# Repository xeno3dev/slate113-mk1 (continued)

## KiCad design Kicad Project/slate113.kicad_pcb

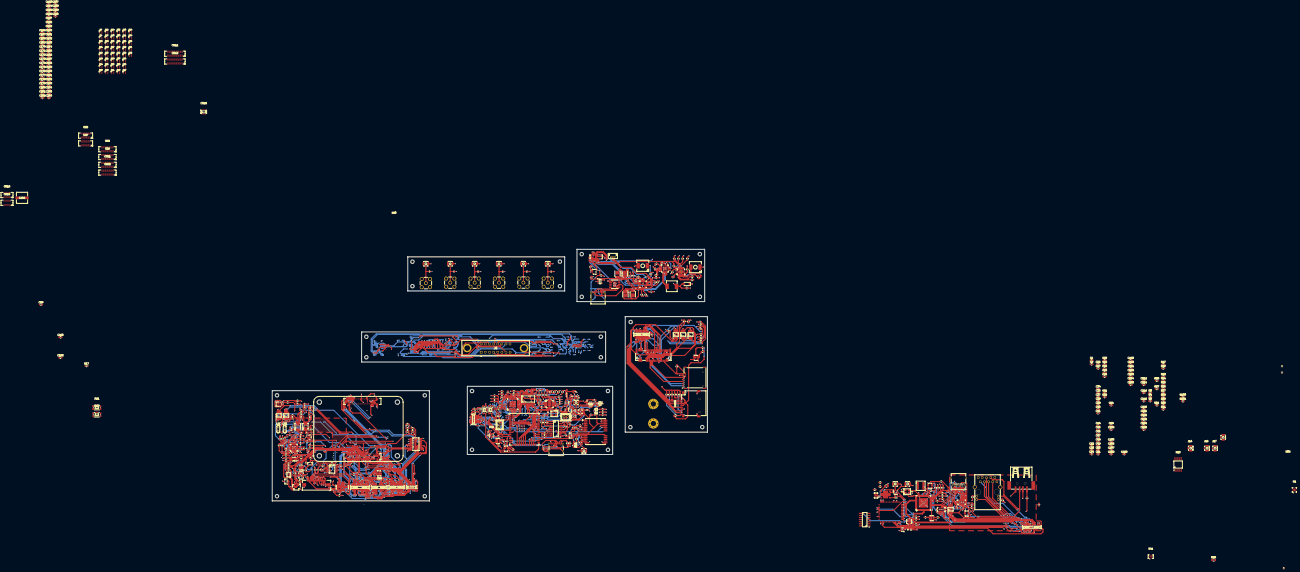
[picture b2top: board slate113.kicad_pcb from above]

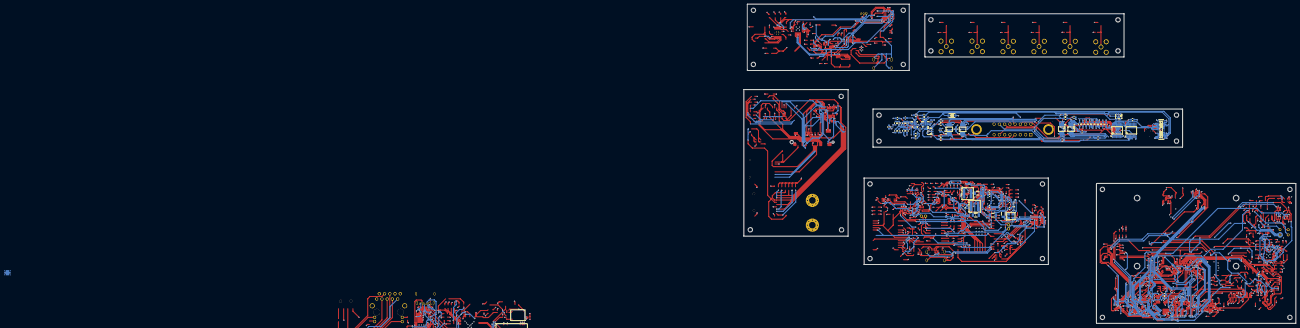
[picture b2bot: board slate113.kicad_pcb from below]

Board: 8 copper layers, 267.6 x 154.7 mm, 611 parts (73 on the bottom side), 545 nets.

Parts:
C1, C94, C106, C108: 0.1µF; C_0603_1608Metric
C2, C8, C9: 1.0µF; C_0603_1608Metric
C3, C11, C68, C71, C91, C217: 4.7µF; C_0603_1608Metric
C4, C5: 47nF; C_0603_1608Metric
C6, C7, C10, C20, C61, C89, C116, C131, C135, C137, C140, C145, C165, C216: 10µF; C_0603_1608Metric
C12, C19, C32, C42, C72, C74, C75, C79, C95, C97, C117, C123, C141, C228: 2.2µF; C_0603_1608Metric
C13, C21, C22, C23, C24, C25, C26, C27, C30, C31, C33, C34, C36, C37, C38, C39, C40, C41, C43, C44, C45, C46, C47, C48, C49, C50, C51, C52, C53, C54, C55, C56, C57, C58, C59, C62, C67, C69, C70, C73, C77, C78, C84, C90, C92, C96, C98, C111, C114, C115, C133, C134, C136, C139, C142, C147, C148, C149, C151, C152, C153, C154, C158, C159, C160, C161, C162, C163, C164, C166, C167, C168, C169, C170, C171, C172, C173, C174, C175, C176, C177, C178, C179, C180, C181, C182, C183, C184, C185, C186, C187, C188, C189, C190, C191, C192, C193, C194, C195, C196, C197, C198, C199, C200, C201, C202, C203, C204, C205, C206, C207, C208, C209, C210, C211, C212, C214, C215, C218, C219, C220, C221, C222, C223, C224, C225, C229, C236: 100nF; C_0603_1608Metric
C14: 8.2nF; C_0603_1608Metric
C15, C18, C76, C118, C120, C121, C124, C129, C130, C132, C138, C144, C150, C155, C239: 1µF; C_0603_1608Metric
C16, C125, C126, C127, C128, C244, C245: 1nF; C_0603_1608Metric
C17: 68pF; C_0603_1608Metric
C28, C29, C35, C66: 15pF; C_0402_1005Metric
C60: 1.8pF; C_0402_1005Metric
C63, C83, C86, C99, C100, C104, C105, C107, C119, C122, C156: 100pF; C_0603_1608Metric
C64: 6.8pF; C_0402_1005Metric
C65, C231: 6.8 pF ± 0.5 pF; C_0402_1005Metric
C80, C240, C242: 10nF; C_0603_1608Metric
C81: 6.8nF; C_0603_1608Metric
C82, C233, C234, C243, C246: 100nF; C_0402_1005Metric
C85, C232: 220 pF ± 5%; C_0402_1005Metric
C87, C88: 33pF; C_0603_1608Metric
C93, C102: 8.2pF; C_0402_1005Metric
C101: 100pF; C_0402_1005Metric
C103: 8.2pF; C_0603_1608Metric
C109, C112: 22pF; C_0402_1005Metric
C110, C113: 22pF; C_0603_1608Metric
C143, C146: 3.3nF; C_0603_1608Metric
C157: 4.7µF/10V/Ceramic; C_0603_1608Metric
C213: 47µF; C_0805_2012Metric
C226, C227: 18pF; C_0402_1005Metric
C230: 12 pF ± 5%; C_0402_1005Metric
C235: 220 µF; CHEMI-F61
C237, C238, C241: 220pF; C_0402_1005Metric
CN1, CN2: DF40C-50DP-0.4V; CONN-SMD_DF40C-50DP-0.4V
CN3, CN7: DF40C-30DS-0.4V; CONN-SMD_DF40C-30DS-0.4V51
CN4, CN6, CN21, CN22: DF40C-40DS-0.4V; CONN-SMD_DF40C-40DS-0.4V51
CN5, CN8, CN9, CN10: DF40C-40DP-0.4V; CONN-SMD_DF40C-40DP-0.4V
CN11, CN14: DF40C-30DP-0.4V; CONN-SMD_30P-P0.40_5001-BM0430-15-00
CN12, CN13: DF40C-50DS-0.4V; CONN-SMD_DF40C-50DS-0.4V51
CN15, CN16: DF40C-24DS-0.4V; CONN-SMD_DF40C-24DS-0.4V51
CN17: 530480310; CONN-TH_0530470310
CN18: DF40C-10DP-0.4V; CONN-SMD_10P-P0.40_DF40C-10DP-0.4V-51
CN19, CN20: DF40C-24DP-0.4V; CONN-SMD_DF40C-24DP-0.4V
Card1: NANO SIM 7P 1.37H PUSH; SIM-SMD_YKSIM-PUSH137-140NANO
Card2: TF PUSH; TF-SMD_TF-PUSH
D1: B5819W; D_SOD-123
D2: RCLAMP0521PATCT; D0402-BI
D3, D4: PESD3V3U1UL; SOD-882_L1.0-W0.6-RD
D5, D6: SP0504BAHTG; SOT-23-5_L3.0-W1.7-P0.95-LS2.8-BR
D7: SMF5.0A_C151296; SOD-123F_L2.8-W1.8-LS3.7-RD
D8, D9, D10, D11, D12, D13, D14, D15, D16, D17, D18, D19, D20, D21, D22, D23, D24, D25, D26, D27, D28, D29, D30, D31, D32, D33, D34, D35, D36, D37, D38, D39, D40, D41, D42, D43, D44, D45, D46, D47, D48, D49, D50, D51, D52: SK9822-EC20
F1: Polyfuse; Fuse_0603_1608Metric
FB1, FB2, FB3, FB5, FB11: FerriteBead; L_0603_1608Metric
FB6, FB7, FB8, FB9: 600Ω @ 100MHz; L_0603_1608Metric
FB10: FerriteBead_Small; L_0603_1608Metric
FPC1: FPC0.5-24P; FPC-SMD_P0.50-24P_XJ-FGS
FPC2: FPC-0.5FX-6PWBH10; FPC-SMD_FPC-0.5FX-6PWBH10
H5, H6: MountingHole_Pad; MountingHole_3.2mm_M3_Pad_Via
J1, J8, J11, J22, J23, J25: RFPC-SMA27-F; GRADCONN_RFPC-SMA27-F
J2: TYPE-C16PIN; USB-C-SMD_TYPE-C16PIN
J3, J7, J10, J12, J24, J26: Conn_Coaxial; U.FL_Hirose_U.FL-R-SMT-1(10)
J4: DF40C-100DP-0.4V51*2; Raspberry-Pi-4-Compute-Module
J6: 395-016-520-202; 395016520202
J9: Bus_M.2_Socket_B; NGFFM_2BKEY_8_2_COPY
J13, J14, J15, J16, J17, J18, J19, J20: U.FL; IPEX-SMD_BWIPX-1-001E
L1: 4.7µH; IND-SMD_L5.5-W5.3
L2, L4: 1µH; IND-SMD_L7.1-W6.5-P5.60
L3: 10µH; IND-SMD_L7.1-W6.6
L5: 5.6nH; L_0402_1005Metric
L6, L7, L9, L10: 33 nH ± 5%; L_0402_1005Metric
L8: 68nH; L_0402_1005Metric
L11, L12: YSPIT0520A-R16M; IND-SMD_L5.5-W5.3
LS1, LS2: Solder Pad; TestPoint_2Pads_Pitch2.54mm_Drill0.8mm
Q1: MMBT3904-TP; SOT-23-3_L2.9-W1.3-P1.90-LS2.4-BR
Q4: MMBT3904-C20526; SOT-23-3_L2.9-W1.3-P1.90-LS2.4-BR
Q5, Q6, Q7, Q8: CSD17575Q3; VSON-CLIP-8_L3.3-W3.3-P0.65-BL
R1: 3.0kΩ (1s, 1.5MHz); R_0603_1608Metric
R2, R25, R31, R32, R33, R36, R37, R47, R50, R52, R53, R54, R55, R64, R74, R75, R76, R84, R88, R90, R94, R96, R100, R102, R108, R109, R110, R112, R113, R114, R115, R116, R117, R118, R119, R120, R122, R124, R126, R127, R128, R129, R130, R131, R134, R135, R136, R137, R138, R139, R140, R141, R153: 10kΩ; R_0603_1608Metric
R3, R4, R27, R42, R62, R63, R97, R98, R132, R133: 4.7kΩ; R_0603_1608Metric
R5, R6, R7, R10, R11, R17, R34, R56, R58, R60, R85, R87, R91, R92, R103, R105: 100kΩ; R_0603_1608Metric
R8: 205kΩ; R_0603_1608Metric
R9: 127kΩ; R_0603_1608Metric
R12: 154kΩ; R_0603_1608Metric
R13: 174kΩ; R_0603_1608Metric
R14: 220kΩ; R_0603_1608Metric
R15: 69.8kΩ; R_0603_1608Metric
R16: 12.1kΩ; R_0603_1608Metric
R18, R19, R20, R21, R22, R23, R26, R38, R44: 47kΩ; R_0603_1608Metric
R24, R142, R143, R144, R145, R146: 50Ω; R_0402_1005Metric
R28: 110Ω; R_0603_1608Metric
R29: 120Ω; R_0603_1608Metric
R30, R65, R66, R68, R69, R77, R78, R79, R80, R81, R82, R83: 22Ω; R_0603_1608Metric
R35: 180kΩ; R_0603_1608Metric
R39: 56kΩ ±1%; R_0603_1608Metric
R40, R41, R104: 5.1kΩ; R_0603_1608Metric
R43, R70: 10Ω; R_0603_1608Metric
R45, R46: 50Ω; R_0805_2012Metric
R48, R49, R51: 52.3Ω; R_0402_1005Metric
R57, R59, R61, R101: 20kΩ; R_0603_1608Metric
R67: 33Ω; R_0603_1608Metric
R71, R72, R73: 1kΩ; R_0603_1608Metric
R86, R93: 402kΩ; R_0603_1608Metric
R89, R95: 3.3kΩ; R_0603_1608Metric
R99: 200kΩ; R_0603_1608Metric
R106, R107: 560Ω; R_0603_1608Metric
R147, R151: 1.5Ω; R_1206_3216Metric
R148, R152: 2.7Ω; R_1206_3216Metric
R149, R150: 2.2kΩ; C_0603_1608Metric
RJ1: HR915350C; RJ45-TH_HR915350C_1
SW1, SW2, SW3, SW4: SW_Push; KEY-SMD_KMR2XXGXXX
U1: FUSB302BMPX; MLP-14_L2.5-W2.5-P0.50-BL-EP
U2: CH224K; SSOP-10-1EP_3.9x4.9mm_P1mm_EP2.1x3.3mm
U3: BQ25792RQMR; QFN-29_L4.0-W4.0-P0.40-TL-BQ25792RQMR
U4: AP2112K-3.3TRG1; SOT-25-5_L2.9-W1.6-P0.95-LS2.8-BL
U5: AP2112K-1.8TRG1; SOT-25_L3.0-W1.6-P0.95-LS2.8-BL
U6: LP8556SQ-E09/NOPB; WQFN-24_L4.0-W4.0-P0.50-BL-EP2.5
U7: HD3SS3220RNHR; WQFN-30_L4.5-W2.5-P0.4-BL-EP
U8: ESD7104MUTAG_C2987068; DFN-10_L2.5-W1.0-P0.50-BL
U9: TPS61088RHLR; VQFN-20_L4.6-W3.6-P0.50-BL
U10, U56, U57, U58: TS3A24159DGSR; MSOP-10_L3.0-W3.0-P0.50-LS5.0-BL
U11, U14, U17, U34, U35, U53, U54: SiP32508DT; TSOT-23-6
U12: PI3USB302-AZBEX; DHVQFN-20_L4.5-W2.5-P0.50-BL-EP
U13: W25Q32JVSSIQ; SOIC-8_L5.3-W5.3-P1.27-LS8.0-BL
U15, U44, U45, U46, U48, U49: TS5A23157DGSR; MSOP-10_L3.0-W3.0-P0.50-LS5.0-BL
U18: GL3523-OTY3C; QFN-76_L9.0-W9.0-P0.40-BL-EP5.8
U19: TXM27.12M0004322DBBDO00T; CRYSTAL-SMD_4P-L3.2-W2.5-BL
U20: CC1101RGPR; QFN-20_L4.0-W4.0-P0.5-TL-EP
U21: 0896BM15A0001001E; SMD6_0896BM15A0001001E_JOT
U22: LC29HBA; LC29H
U23: EM4095HMSO16B+; SOIC-16_L9.9-W3.9-P1.27-LS6.0-BL
U24, U25, U26, U27, U30, U36: PE4259-63; SC-70-6_L2.2-W1.3-P0.65-LS2.1-BL
U28: 0433BM15A0001001E; SMD6_0896BM15A0001001E_JOT
U29: PN7160A1HN/C100E; HVQFN-40_L6.0-W6.0-P0.50-BL-EP4.1
U31, U73: B2B-PH-K-S; CONN-TH_B2B-PH-K-S
U33: ESP32-S3-WROOM-1U-N16R2; WIRELM-SMD_ESP32-S3-WROOM-1U
U37: CPL0605AT13R2455A
U38: X4C60K1-20SR; X4C60K1-20S
U39: XEC24P3-30GR; XEC24P3-30G
U40, U41, U42: AD8317ACPZ-R7; LFCSP-8_L3.0-W2.0-P0.50-BL-EP
U43: LM339D; SOIC-14_L8.7-W3.9-P1.27-LS6.0-BL
U47: ES8388; QFN-28_L4.0-W4.0-P0.45-BL-EP
U50, U51: PAM8302AASCR; MSOP-8_L3.0-W3.0-P0.65-LS5.0-BL
U52: TPS7A0233PDBVR; SOT-23-5_L2.9-W1.6-P0.95-LS2.8-BR
U55, U61: TCA9534APWR; TSSOP-16_L5.0-W4.4-P0.65-LS6.4-BL
U59, U60: TPS259470ARPWR; VQFN-10_L2.0-W2.0-P0.45-TL
U62: PCA9306DCUR; SSOP-8_L2.0-W2.3-P0.50-LS3.1-BR
U63: AP2120N-2.8TRG1; SOT-23-3_L2.9-W1.3-P1.90-LS2.4-BR
U64, U69: TCA9535PWR; TSSOP-24_L7.8-W4.4-P0.65-LS6.4-BL
U65: MSM381ADB001; MIC-SMD_5P_L3.5-W2.7-P0.82_MSM381ADB001
U66: DF40B-10DS-0.4V; CONN-SMD_10P-P0.40_DF40B-10DS-0.4V-51
U67: SIP32508DT-T1-GE3; TSOT-23-6_L2.9-W1.6-P0.95-LS2.8-BR
U68: SN74AHCT125PWR; TSSOP-14_L5.0-W4.4-P0.65-LS6.4-BL
U70: SkyLab WG243; WG243
U71: SKY13373-460LF; QFN-12_L2.0-W2.0-P0.50-BL-EP
U72: SN74AXC1T45DCKR; SC-70-6_L2.0-W1.3-P0.65-LS2.1-BL-1
USB1: TYPE-C 24P QCHT; TYPE-C-SMD_TYPE-C-24P-QCHT
USB2: TYPE-C16PIN; USB-C-SMD_TYPE-C16PIN
USB3: BX-TYPE-A-MWT4P; USB-A-SMD_BX-TYPE-A-MWT4P
X1: X322525MOB4SI; CRYSTAL-SMD_4P-L3.2-W2.5-BL_X322525MOB4SI
Y3: 26.0MHz; CRYSTAL-SMD_4P-L3.2-W2.5-BL

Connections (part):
1V8: C111.1, CN3.5, CN4.38, CN6.38, CN7.5, CN9.38, CN10.38, CN11.5, CN14.5, FPC1.22, J4.88, J4.90, R62.1, R63.2, R71.2, R72.2, R96.1, R97.2, R98.1, R100.2, U5.5 (VOUT), U44.8 (V+), U45.8 (V+), U46.8 (V+), U47.2 (DVDD), U47.3 (PVDD), U48.8 (V+), U49.8 (V+), U62.2 (VREF1)
2.4G_SENSE: CN1.47, CN1.48, CN2.47, CN2.48, CN12.47, CN12.48, CN13.47, CN13.48, J4.47, J4.94, R53.2, R54.2, U43.1, U43.2
3V3: C1.1, C2.1, C8.1, C9.1, C12.1, C19.1, C22.2, C23.2, C24.2, C30.1, C34.1, C41.1, C42.1, C59.2, C82.1, C94.1, C95.1, C99.1, C105.1, C106.1, C107.1, C108.1, C141.1, C148.1, C149.1, C150.1, C151.1, C152.1, C153.1, C154.1, C158.1, C159.1, C160.1, C161.1, C225.1, C233.1, CN1.6, CN1.7, CN2.6, CN2.7, CN3.4, CN4.25, CN5.11, CN6.25, CN7.4, CN8.11, CN9.25, CN10.25, CN11.4, CN12.6, CN12.7, CN13.6, CN13.7, CN14.4, CN15.14, CN16.14, CN19.14, CN20.14, CN21.11, CN22.11, FPC1.23, J4.84, J4.86, J6.3, L4.1, R3.1, R4.1, R7.1, R18.2, R19.2, R20.2, R21.2, R22.2, R23.2, R25.1, R27.1, R28.1, R29.1, R31.1, R32.1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
5V: C97.1, CN15.12, CN16.12, CN20.12
315MHZ_OUT: C232.1, U71.1 (J1)
433MHZ_OUT: U28.1 (UNBALANCEDPORT), U71.9 (J2)
868/915MHZ_OUT: C63.1, U71.3 (J3)
ACC_AUX0: R82.2, U56.3 (COM1)
ACC_AUX1: R83.2, U56.9 (COM2)
ACC_CS0_N: R78.2, U58.9 (COM2)
ACC_IRQ0: R77.2, U57.3 (COM1)
ACC_MISO: R81.2, U58.3 (COM1)
ACC_MOSI: R80.2, U10.9 (COM2)
ACC_RESET_N: R79.2, U57.9 (COM2)
ACC_SCK: R30.2, U10.3 (COM1)
ACDVR1: Q5.4 (G), Q6.4 (G), U3.11 (ACDRV1)
ACDVR2: Q7.4 (G), Q8.4 (G), U3.10 (ACDRV2)
AMP_L_SD: C131.1, C133.1, R74.2, U50.1 (~SD), U69.8 (P04)
AMP_R_SD: C134.1, C135.1, R75.2, U51.1 (~SD), U69.9 (P05)
AUDIO_3V3: C115.1, C116.1, C138.2, R70.2, U47.17 (AVDD), U52.5 (OUT)
AUDIO_ASDOUT: U47.8 (ASDOUT), U49.6 (COM2)
AUDIO_DSDIN: U47.6 (DSDIN), U49.10 (COM1)
AUDIO_I2C_SCL: R62.2, R72.1, U44.4 (NO2), U47.28 (CCLK)
AUDIO_I2C_SDA: R63.1, R71.1, U44.2 (NO1), U47.27 (CDATA)
AUDIO_LOUT1: C130.2, U47.12 (LOUT1)
AUDIO_LRCK: U47.7 (LRCK), U48.6 (COM2)
AUDIO_PCM_CLK: R65.1, U45.2 (NO1)
AUDIO_PCM_CLK_F: C109.1, CN4.21, CN6.21, CN9.21, CN10.21, R65.2, U48.2 (NO1)
AUDIO_PCM_IN: R68.1, U46.2 (NO1)
AUDIO_PCM_IN_F: C112.1, CN4.31, CN6.31, CN9.31, CN10.31, R68.2, U49.4 (NO2)
AUDIO_PCM_OUT: R69.1, U46.4 (NO2)
AUDIO_PCM_OUT_F: C113.1, CN4.30, CN6.30, CN9.30, CN10.30, R69.2, U49.2 (NO1)
AUDIO_PCM_SYNC: R66.1, U45.4 (NO2)
AUDIO_PCM_SYNC_F: C110.1, CN4.32, CN6.32, CN9.32, CN10.32, R66.2, U48.4 (NO2)
AUDIO_ROUT1: C129.1, U47.11 (ROUT1)
AUDIO_SCLK: U47.5 (SCLK), U48.10 (COM1)
AUDIO_VREF: C121.2, U47.10 (VREF)
AVDD9_CAP: C240.2, U20.9 (AVDD)
AVDD11_CAP: C237.2, U20.11 (AVDD)
AVDD14_CAP: C242.2, U20.14 (AVDD)
AVDD15_CAP: C238.2, U20.15 (AVDD)
BADUSB_DM: U33.13 (IO19), USB2.A7 (DN1), USB2.B7 (DN2)
BADUSB_DP: U33.14 (IO20), USB2.A6 (DP1), USB2.B6 (DP2)
BAND_SEL_1: U26.4 (CTRL), U27.4 (CTRL), U64.6 (P02)
BAND_SEL_2: U24.4 (CTRL), U25.4 (CTRL), U64.7 (P03)
BLE_ANT1: U36.5 (RFC), U70.12 (BT)
BLE_CPL: R51.2, U37.4 (Coupled_Out)
BLE_CTRL: CN1.46, CN2.46, CN12.46, CN13.46, J4.49, U36.4 (CTRL)
BLE_DET: U42.4 (VSET), U42.5 (VOUT), U43.8
BLE_REF: R60.2, R61.1, U43.9
BLE_SENSE: CN1.49, CN2.49, CN12.49, CN13.49, J4.96, R55.2, U43.14
BLE_SMA_ANT: J14.1 (In), U37.3 (Output)
BLE_SW_SMA: U36.3 (RF2), U37.2 (Input)
BOOT: SW4.2, U33.27 (IO0)
BQ_INT: CN3.7, CN7.7, CN11.7, CN14.7, J4.19, U3.21 (~INT)
BT_EN: CN1.19, CN2.19, CN12.19, CN13.19, R131.1, U69.4 (P00), U70.38 (BT_DISn)
CC_GDO0: U20.6 (GDO0(ATEST)), U33.6 (IO6)
CC_GDO2: U20.3 (GDO2), U33.25 (IO48)
CM5_5V: C31.2, C32.1, C132.2, C136.1, C137.1, C139.1, C140.1, C215.1, C217.1, C219.1, C228.1, CN1.4, CN1.5, CN2.4, CN2.5, CN3.2, CN3.3, CN7.2, CN7.3, CN11.2, CN11.3, CN12.4, CN12.5, CN13.4, CN13.5, CN14.2, CN14.3, CN19.12, F1.1, J4.77, J4.79, J4.81, J4.83, J4.85, J4.87, R14.2, R109.2, U9.14 (VOUT), U9.15 (VOUT), U9.16 (VOUT), U50.6 (VDD), U51.6 (VDD), U52.1 (IN), U52.3 (EN), U67.5 (IN), U67.6 (IN), U68.10 (~3OE), U68.13 (~4OE), U68.14 (VCC)
CM5_ACC_AUX0: CN5.28, CN8.28, CN21.28, CN22.28, J4.56, U56.5 (NC1)
CM5_ACC_AUX1: CN5.29, CN8.29, CN21.29, CN22.29, J4.36, U56.7 (NC2)
CM5_ACC_CS0_N: CN5.25, CN8.25, CN21.25, CN22.25, J4.31, U58.7 (NC2)
CM5_ACC_IRQ0: CN5.26, CN8.26, CN21.26, CN22.26, J4.35, U57.5 (NC1)
CM5_ACC_MISO: CN5.24, CN8.24, CN21.24, CN22.24, J4.29, U58.5 (NC1)
CM5_ACC_MOSI: CN5.23, CN8.23, CN21.23, CN22.23, J4.27, U10.7 (NC2)
CM5_ACC_RESET_N: CN5.27, CN8.27, CN21.27, CN22.27, J4.54, U57.7 (NC2)
CM5_ACC_SCK: CN5.22, CN8.22, CN21.22, CN22.22, J4.25, U10.5 (NC1)
CM5_SAI_LRCK: J4.28, U48.7 (NC2)
CM5_SAI_MCLK: J4.24, R67.1
CM5_SAI_SCLK: J4.26, U48.9 (NC1)
CM5_SAI_SDI: J4.30, U49.7 (NC2)
CM5_SAI_SDO: J4.34, U49.9 (NC1)
CM5_UART_RX: CN15.17, CN16.17, CN19.17, CN20.17, J4.95, U33.11 (IO18)
CM5_UART_TX: CN15.19, CN16.19, CN19.19, CN20.19, J4.21, U33.10 (IO17)
COMBO_EN: CN1.22, CN2.22, CN12.22, CN13.22, U69.7 (P03), U70.24 (RESET)
COMP: C16.1, C17.1, R16.1, U9.18 (COMP)
DP_SS_RXN: CN1.34, CN2.34, CN12.34, CN13.34, J4.148 (48), U12.12 (Rx2-)
DP_SS_RXP: CN1.33, CN2.33, CN12.33, CN13.33, J4.146 (46), U12.13 (Rx2+)
DP_SS_TXN: CN1.32, CN2.32, CN12.32, CN13.32, J4.106 (6), U12.14 (Tx2-)
DP_SS_TXP: CN1.31, CN2.31, CN12.31, CN13.31, J4.104 (4), U12.15 (Tx2+)
DSI_CLKN: FPC1.9, J4.187 (87)
DSI_CLKP: FPC1.10, J4.189 (89)
DSI_D0N: FPC1.6, J4.175 (75)
DSI_D0P: FPC1.7, J4.177 (77)
DSI_D1N: FPC1.12, J4.181 (81)
DSI_D1P: FPC1.13, J4.183 (83)
DSI_D2N: FPC1.15, J4.193 (93)
DSI_D2P: FPC1.16, J4.195 (95)
DSI_D3N: FPC1.3, J4.194 (94)
DSI_D3P: FPC1.4, J4.196 (96)
EM_DEMOD_OUT: U23.13 (DEMOD_OUT), U33.4 (IO4)
EM_MOD: U23.12 (MOD), U33.32 (IO39)
EM_RDY_CLK: U23.2 (RDY/CLK), U33.23 (IO21)
EM_SHD: R112.1, U23.14 (SHD), U64.9 (P05)
ESP_RST: C57.2, CN15.15, CN16.15, CN19.15, CN20.15, J4.97, R104.2, SW3.2, U33.3 (EN)
ETH_MDI0N: CN1.8, CN2.8, CN12.8, CN13.8, J4.10, RJ1.1
ETH_MDI0P: CN1.9, CN2.9, CN12.9, CN13.9, J4.12, RJ1.2
ETH_MDI1N: CN1.10, CN2.10, CN12.10, CN13.10, J4.6, RJ1.3
ETH_MDI1P: CN1.13, CN2.13, CN12.13, CN13.13, J4.4, RJ1.6
ETH_MDI2N: CN1.11, CN2.11, CN12.11, CN13.11, J4.9, RJ1.4
ETH_MDI2P: CN1.12, CN2.12, CN12.12, CN13.12, J4.11, RJ1.5
ETH_MDI3N: CN1.14, CN2.14, CN12.14, CN13.14, J4.5, RJ1.7
ETH_MDI3P: CN1.15, CN2.15, CN12.15, CN13.15, J4.3, RJ1.8
FerriteGND_Carrier: CN2.51, CN2.52, CN2.53, CN2.54, CN10.41, CN10.42, CN10.43, CN10.44, CN11.31, CN11.32, CN11.33, CN11.34, CN19.25, CN19.26, CN19.27, CN19.28, FB2.1
FerriteGND_IO: CN1.51, CN1.52, CN1.53, CN1.54, FB3.1, RJ1.15 (SHELL), RJ1.16 (SHELL), USB1.25 (EH), USB3.5, USB3.6
FerriteGND_M.2: CN9.41, CN9.42, CN9.43, CN9.44, FB10.2
FerriteGND_PWR: CN14.31, CN14.32, CN14.33, CN14.34, FB1.1, J2.1 (SHELL), J2.2 (SHELL), J2.3 (SHELL), J2.4 (SHELL)
FerriteGND_RADIO: CN20.25, CN20.26, CN20.27, CN20.28, FB5.1, FB11.1, USB2.1 (SHELL), USB2.2 (SHELL), USB2.3 (SHELL), USB2.4 (SHELL)
GND: C3.1, C6.2, C7.2, C8.2, C9.2, C10.2, C11.2, C12.2, C14.1, C15.1, C16.2, C17.2, C18.2, C20.2, C22.1, C23.1, C24.1, C25.1, C26.1, C27.1, C28.1, C29.1, C34.2, C35.1, C36.2, C37.2, C38.2, C39.2, C40.2, C41.2, C44.2, C45.2, C46.2, C47.2, C48.2, C49.2, C50.2, C51.2, C52.2, C53.2, C54.2, C55.2, C56.2, C57.1, C58.1, C59.1, C61.1, C62.1, C65.2, C66.2, C68.1, C69.1, C71.1, C72.1, C73.1, C74.1, C75.1, C76.1, C78.1, C79.1, C80.1, C81.1, C82.2, C83.2, C84.1, C85.2, C87.2, C88.2, C89.2, C90.2, C91.2, C92.2, C93.2, C94.2, C99.2, C102.2, C103.2, C105.2, C106.2, C107.2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
GPS_1PPS: U22.3 (1PPS), U33.24 (IO47)
GPS_ANT: C86.1, D2.2 (A), J20.1 (In), L8.2
GPS_RESET: R44.1, U64.8 (P04)
GPS_RESET_N: Q1.3 (C), R42.2, U22.8 (RESET_N)
GPS_RF_IN: C86.2, U22.11 (RF_IN)
GPS_UART_RX: U33.8 (IO15), U72.3 (A)
GPS_UART_RX_F: U22.21 (RXD1/SPI_MOSI), U72.4 (B)
GPS_UART_TX: U22.20 (TXD1/SPI_MISO), U33.9 (IO16)
GPS_VBCKP: C58.2, C68.2, C69.2, C71.2, C76.2, C87.1, C88.1, C89.1, C90.1, C91.1, C92.1, C96.1, C236.1, C239.1, D3.2 (A), D4.2 (A), R42.1, R104.1, R132.2, R133.1, U20.4 (DVDD), U22.22 (V_BCKP), U22.23 (VCC), U24.6 (CTRL#orVDD), U25.6 (CTRL#orVDD), U26.6 (CTRL#orVDD), U27.6 (CTRL#orVDD), U29.6 (VDD(PAD)), U29.12 (VBAT2), U29.13 (VDD(UP)), U29.28 (VBAT), U33.2 (3V3), U64.24 (VCC)
GPS_VDD_RF: R43.1, U22.9 (VDD_RF)
GPS_WAKEUP: U22.1 (WAKEUP), U33.5 (IO5)
GPS_WI: U22.17 (WI), U33.29 (IO36)
HUB_1V2: C162.1, C163.1, C164.1, C165.1, C220.1, C221.1, C222.1, C223.1, C224.1, L1.1, U18.4 (AVDD12), U18.7 (VP12_P4), U18.17 (VP12_P3), U18.22 (VP12_P2), U18.28 (DVDD12), U18.39 (FB), U18.47 (DVDD12), U18.60 (VP12_P1), U18.70 (VP12_P0)
HUB_5V: C212.1, C214.1, C216.1, C218.1, C229.1, U18.42 (VDDP), U18.43 (V5), U18.54 (VBUS)
HUB_CLK: U13.6 (CLK), U18.50 (P_SPI_CK)
HUB_CS#: U13.1 (~CS), U18.52 (P_SPI_CZ)
HUB_DI: U13.5 (DI(IO0)), U18.51 (P_SPI_DI)
HUB_DO: U13.2 (DO(IO1)), U18.49 (P_SPI_DO)
I2C0_SCL: CN1.37, CN2.37, CN3.8, CN7.8, CN8.13, CN11.8, CN12.37, CN13.37, CN14.8, J4.44, R27.2, U1.6 (SCL), U3.14 (SCL), U6.6 (SCL), U62.6 (SCL2), U69.22 (SCL)
I2C0_SDA: CN1.38, CN2.38, CN3.9, CN7.9, CN8.12, CN11.9, CN12.38, CN13.38, CN14.9, J4.46, R4.2, U1.7 (SDA), U3.15 (SDA), U6.5 (SDA), U62.5 (SDA2), U69.23 (SDA)
I2C_SCL: J9.56 (SCL), U44.6 (COM2)
I2C_SDA: J9.58 (SDA), U44.10 (COM1)
J2_CC1: J2.A5 (CC1), U2.7 (CC1)
J2_CC2: J2.B5 (CC2), U2.6 (CC2)
J2_VBUS: J2.A4B9 (VBUS), J2.B4A9 (VBUS), U2.8 (VBUS)
L1P1: L3.1, U6.1 (SW), U6.2 (SW)
L3_BOOST: C13.1, L4.2, U9.4 (SW), U9.5 (SW), U9.6 (SW), U9.7 (SW)
LAN0_GLED+: CN1.16, CN2.16, CN12.16, CN13.16, J4.17, RJ1.13
LAN0_YLED-: CN1.17, CN2.17, CN12.17, CN13.17, J4.15, RJ1.12
LCD_LED_A: CN11.20, FPC1.21
LCD_LED_K: CN3.21, CN7.21, CN11.21, CN14.21, FPC1.20, U6.12 (LED1), U6.13 (LED2)
LCD_PWM: CN3.19, CN7.19, CN11.19, CN14.19, FPC1.18, U6.9 (PWM)
LCD_RST_L: C147.1, FPC1.19, J4.39, R96.2
LED_5V: C166.2, C167.2, C168.2, C169.2, C170.2, C171.2, C172.2, C173.2, C174.2, C175.2, C176.2, C177.2, C178.2, C179.2, C180.2, C181.2, C182.2, C183.2, C184.2, C185.2, C186.2, C187.2, C188.2, C189.2, C190.2, C191.2, C192.2, C193.2, C194.2, C195.2, C196.2, C197.2, C198.2, C199.2, C200.2, C201.2, C202.2, C203.2, C204.2, C205.2, C206.2, C207.2, C208.2, C209.2, C210.2, C211.1, C213.1, C235.1, CN18.1, CN18.3, CN18.9, CN18.10, D8.5 (VDD), D9.5 (VDD), D10.5 (VDD), D11.5 (VDD), D12.5 (VDD), D13.5 (VDD), D14.5 (VDD), D15.5 (VDD), D16.5 (VDD), D17.5 (VDD), D18.5 (VDD), D19.5 (VDD), D20.5 (VDD), D21.5 (VDD), D22.5 (VDD), D23.5 (VDD), D24.5 (VDD), D25.5 (VDD), D26.5 (VDD), D27.5 (VDD), D28.5 (VDD), D29.5 (VDD), D30.5 (VDD), D31.5 (VDD), D32.5 (VDD), D33.5 (VDD), D34.5 (VDD), D35.5 (VDD)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
LED_BUF_BASE: Q4.1 (B), R108.1
LED_BUF_OE_N: Q4.3 (C), R109.1, U68.1 (~1OE), U68.4 (~2OE)
LED_CLK_1_OUT: D8.6 (CKO), D9.4 (CKI)
LED_CLK_2_OUT: D9.6 (CKO), D10.4 (CKI)
LED_CLK_3V3: CN15.22, CN16.22, CN19.22, CN20.22, U33.35 (IO42), U68.5 (2A)
LED_CLK_3_OUT: D10.6 (CKO), D11.4 (CKI)
LED_CLK_4_OUT: D11.6 (CKO), D12.4 (CKI)
LED_CLK_5V: R107.1, U68.6 (2Y)
LED_CLK_5_OUT: D12.6 (CKO), D13.4 (CKI)
LED_CLK_6_OUT: D13.6 (CKO), D14.4 (CKI)
LED_CLK_7_OUT: D14.6 (CKO), D15.4 (CKI)
LED_CLK_8_OUT: D15.6 (CKO), D16.4 (CKI)
LED_CLK_9_OUT: D16.6 (CKO), D17.4 (CKI)
LED_CLK_10_OUT: D17.6 (CKO), D18.4 (CKI)
LED_CLK_11_OUT: D18.6 (CKO), D19.4 (CKI)
LED_CLK_12_OUT: D19.6 (CKO), D20.4 (CKI)
LED_CLK_13_OUT: D20.6 (CKO), D21.4 (CKI)
LED_CLK_14_OUT: D21.6 (CKO), D22.4 (CKI)
LED_CLK_15_OUT: D22.6 (CKO), D23.4 (CKI)
LED_CLK_16_OUT: D23.6 (CKO), D24.4 (CKI)
LED_CLK_17_OUT: D24.6 (CKO), D25.4 (CKI)
LED_CLK_18_OUT: D25.6 (CKO), D26.4 (CKI)
LED_CLK_19_OUT: D26.6 (CKO), D27.4 (CKI)
LED_CLK_20_OUT: D27.6 (CKO), D28.4 (CKI)
LED_CLK_21_OUT: D28.6 (CKO), D29.4 (CKI)
LED_CLK_22_OUT: D29.6 (CKO), D30.4 (CKI)
LED_CLK_23_OUT: D30.6 (CKO), D31.4 (CKI)
LED_CLK_24_OUT: D31.6 (CKO), D32.4 (CKI)
LED_CLK_25_OUT: D32.6 (CKO), D33.4 (CKI)
LED_CLK_26_OUT: D33.6 (CKO), D34.4 (CKI)
LED_CLK_27_OUT: D34.6 (CKO), D35.4 (CKI)
LED_CLK_28_OUT: D35.6 (CKO), D36.4 (CKI)
LED_CLK_29_OUT: D36.6 (CKO), D37.4 (CKI)
LED_CLK_30_OUT: D37.6 (CKO), D38.4 (CKI)
LED_CLK_31_OUT: D38.6 (CKO), D39.4 (CKI)
LED_CLK_32_OUT: D39.6 (CKO), D40.4 (CKI)
LED_CLK_33_OUT: D40.6 (CKO), D41.4 (CKI)
LED_CLK_34_OUT: D41.6 (CKO), D42.4 (CKI)
LED_CLK_35_OUT: D42.6 (CKO), D43.4 (CKI)
LED_CLK_36_OUT: D43.6 (CKO), D45.4 (CKI)
LED_CLK_37_OUT: D44.4 (CKI), D45.6 (CKO)
LED_CLK_38_OUT: D44.6 (CKO), D46.4 (CKI)
LED_CLK_39_OUT: D46.6 (CKO), D47.4 (CKI)
LED_CLK_40_OUT: D47.6 (CKO), D48.4 (CKI)
LED_CLK_41_OUT: D48.6 (CKO), D49.4 (CKI)
LED_CLK_42_OUT: D49.6 (CKO), D50.4 (CKI)
LED_CLK_43_OUT: D50.6 (CKO), D51.4 (CKI)
LED_CLK_44_OUT: D51.6 (CKO), D52.4 (CKI)
LED_CLK_IN: CN18.6, D8.4 (CKI), R107.2, U66.6
LED_DATA_1_OUT: D8.1 (SDO), D9.3 (SDI)
LED_DATA_2_OUT: D9.1 (SDO), D10.3 (SDI)
LED_DATA_3V3: CN15.21, CN16.21, CN19.21, CN20.21, U33.34 (IO41), U68.2 (1A)
LED_DATA_3_OUT: D10.1 (SDO), D11.3 (SDI)
LED_DATA_4_OUT: D11.1 (SDO), D12.3 (SDI)
LED_DATA_5V: R106.1, U68.3 (1Y)
LED_DATA_5_OUT: D12.1 (SDO), D13.3 (SDI)
LED_DATA_6_OUT: D13.1 (SDO), D14.3 (SDI)
LED_DATA_7_OUT: D14.1 (SDO), D15.3 (SDI)
LED_DATA_8_OUT: D15.1 (SDO), D16.3 (SDI)
LED_DATA_9_OUT: D16.1 (SDO), D17.3 (SDI)
LED_DATA_10_OUT: D17.1 (SDO), D18.3 (SDI)
LED_DATA_11_OUT: D18.1 (SDO), D19.3 (SDI)
LED_DATA_12_OUT: D19.1 (SDO), D20.3 (SDI)
LED_DATA_13_OUT: D20.1 (SDO), D21.3 (SDI)
LED_DATA_14_OUT: D21.1 (SDO), D22.3 (SDI)
LED_DATA_15_OUT: D22.1 (SDO), D23.3 (SDI)
LED_DATA_16_OUT: D23.1 (SDO), D24.3 (SDI)
LED_DATA_17_OUT: D24.1 (SDO), D25.3 (SDI)
LED_DATA_18_OUT: D25.1 (SDO), D26.3 (SDI)
LED_DATA_19_OUT: D26.1 (SDO), D27.3 (SDI)
LED_DATA_20_OUT: D27.1 (SDO), D28.3 (SDI)
LED_DATA_21_OUT: D28.1 (SDO), D29.3 (SDI)
LED_DATA_22_OUT: D29.1 (SDO), D30.3 (SDI)
LED_DATA_23_OUT: D30.1 (SDO), D31.3 (SDI)
LED_DATA_24_OUT: D31.1 (SDO), D32.3 (SDI)
LED_DATA_25_OUT: D32.1 (SDO), D33.3 (SDI)
LED_DATA_26_OUT: D33.1 (SDO), D34.3 (SDI)
LED_DATA_27_OUT: D34.1 (SDO), D35.3 (SDI)
LED_DATA_28_OUT: D35.1 (SDO), D36.3 (SDI)
LED_DATA_29_OUT: D36.1 (SDO), D37.3 (SDI)
LED_DATA_30_OUT: D37.1 (SDO), D38.3 (SDI)
LED_DATA_31_OUT: D38.1 (SDO), D39.3 (SDI)
LED_DATA_32_OUT: D39.1 (SDO), D40.3 (SDI)
LED_DATA_33_OUT: D40.1 (SDO), D41.3 (SDI)
LED_DATA_34_OUT: D41.1 (SDO), D42.3 (SDI)
LED_DATA_35_OUT: D42.1 (SDO), D43.3 (SDI)
LED_DATA_36_OUT: D43.1 (SDO), D45.3 (SDI)
LED_DATA_37_OUT: D44.3 (SDI), D45.1 (SDO)
LED_DATA_38_OUT: D44.1 (SDO), D46.3 (SDI)
LED_DATA_39_OUT: D46.1 (SDO), D47.3 (SDI)
LED_DATA_40_OUT: D47.1 (SDO), D48.3 (SDI)
LED_DATA_41_OUT: D48.1 (SDO), D49.3 (SDI)
LED_DATA_42_OUT: D49.1 (SDO), D50.3 (SDI)
LED_DATA_43_OUT: D50.1 (SDO), D51.3 (SDI)
LED_DATA_44_OUT: D51.1 (SDO), D52.3 (SDI)
LED_DATA_IN: CN18.7, D8.3 (SDI), R106.2, U66.7
LED_PWR_EN: CN15.23, CN16.23, CN19.23, CN20.23, R105.1, R108.2, R110.1, U64.4 (P00), U67.3 (EN)
M2_3V3: C21.1, CN4.2, CN6.2, CN9.2, CN10.2, J9.2 (3.3V), J9.4 (3.3V), J9.70 (3.3V), J9.72 (3.3V), J9.74 (3.3V)
M2_DM: CN1.27, CN2.27, CN4.17, CN6.17, CN9.17, CN10.17, CN12.27, CN13.27, J9.9 (USB_D-), U18.14 (DM_P3)
M2_DP: CN1.26, CN2.26, CN4.16, CN6.16, CN9.16, CN10.16, CN12.26, CN13.26, J9.7 (USB_D+), U18.13 (DP_P3)
M2_EN: CN1.40, CN2.40, CN12.40, CN13.40, J4.64, U11.3 (EN), U18.33 (PWREN3J)
M2_PWROFF: CN4.3, CN6.3, CN9.3, CN10.3, J4.68, J9.6 (~FULL_CARD_POWER_OFF)
MIC_BIAS: C123.1, R73.2, U65.5 (VDD)
MIC_OUT: C124.1, U65.1 (OUT)
MIC_OUT_AC: C120.1, C122.2, C124.2
MODEM_AUDIO_EN: CN4.34, CN6.34, CN9.34, CN10.34, R64.2, U44.1 (IN1), U44.5 (IN2), U45.1 (IN1), U45.5 (IN2), U46.1 (IN1), U46.5 (IN2), U48.1 (IN1), U48.5 (IN2), U49.1 (IN1), U49.5 (IN2), U69.11 (P07)
MODEM_RESET_N: CN4.37, CN6.37, CN9.37, CN10.37, J4.51, J9.67 (~RESET)
MODEM_WAKE: CN4.35, CN6.35, CN9.35, CN10.35, J4.55, J9.23 (GPIO_11)
MODEM_W_DISABLE: CN4.36, CN6.36, CN9.36, CN10.36, J9.8 (~W_DISABLE1), U69.13 (P10)
NFC_ANT1: R148.2, R149.2, U29.23 (ANT1), U31.1
NFC_ANT2: R150.2, R152.2, U29.24 (ANT2), U31.2
NFC_IRQ: U29.8 (IRQ), U33.30 (IO37)
NFC_RX_N: C245.1, U29.15 (RXN)
NFC_RX_P: C244.1, U29.16 (RXP)
NFC_TX1: R147.1, U29.21 (TX1)
NFC_TX2: R151.1, U29.19 (TX2)
NFC_VDDCORE: C75.2, C79.2, U29.26 (VDD(A)), U29.27 (VDD), U29.31 (VDD(D))
NFC_VDDTX: C72.2, C74.2, U29.14 (VDD(TX)), U29.18 (TVDD_IN), U29.22 (VDD_IN2)
NFC_VEN: R114.1, U29.10 (VEN), U64.14 (P11)
NFC_VMID: C73.2, U29.17 (VDD(VMID))
NFC_XTAL1: C66.1, U19.1, U29.29 (XTAL2)
NFC_XTAL2: C35.2, U19.3, U29.30 (NFC_CLK_XTAL1)
NPN_B: Q1.1 (B), R44.2
unnamed: C1.2, C2.2, U1.3 (VDD), U1.4 (VDD)
unnamed: C19.2, U11.5 (IN), U11.6 (IN)
unnamed: C21.2, U11.1 (OUT), U11.2 (OUT)
unnamed: C32.2, U14.5 (IN), U14.6 (IN)
unnamed: C33.2, U14.1 (OUT), U14.2 (OUT)
unnamed: C42.2, U17.5 (IN), U17.6 (IN)
unnamed: C43.2, U17.1 (OUT), U17.2 (OUT)
unnamed: C60.1, C63.2
unnamed: C60.2, L5.1
unnamed: C64.2, L7.2, L9.1
unnamed: C83.1, C84.2, L8.1, R43.2
unnamed: C85.1, L6.2
unnamed: C95.2, U34.5 (IN), U34.6 (IN)
unnamed: C96.2, U34.1 (OUT), U34.2 (OUT)
unnamed: C97.2, U35.5 (IN), U35.6 (IN)
unnamed: C98.2, U35.1 (OUT), U35.2 (OUT)
unnamed: C100.1, R48.1
unnamed: C101.1, R49.1
unnamed: C104.1, R51.1
unnamed: C141.2, U54.5 (IN), U54.6 (IN)
unnamed: C142.2, U54.1 (OUT), U54.2 (OUT)
unnamed: C228.2, U53.5 (IN), U53.6 (IN)
unnamed: C229.2, U53.1 (OUT), U53.2 (OUT)
unnamed: C230.2, L9.2, L10.2
unnamed: C231.2, C232.2, L10.1
unnamed: C243.1, R148.1
unnamed: C243.2, L11.1
unnamed: C244.2, R149.1
unnamed: C245.2, R150.1
unnamed: C246.1, R152.1
unnamed: C246.2, L12.1
unnamed: J1.1, J3.1 (In), R143.2
unnamed: J4.101 (1), R17.2
unnamed: J7.1 (In), J22.1, R24.2
unnamed: J8.1, J10.1 (In), R145.2
unnamed: J11.1, J12.1 (In), R146.2
unnamed: J15.1 (In), U30.1 (RF1)
unnamed: J16.1 (In), U36.1 (RF1)
unnamed: J23.1, J24.1 (In), R142.2
unnamed: J25.1, J26.1 (In), R144.2
unnamed: L11.2, R147.2
unnamed: L12.2, R151.2
unnamed: Q5.1 (S), Q5.2 (S), Q5.3 (S), Q6.1 (S), Q6.2 (S), Q6.3 (S)
unnamed: Q7.1 (S), Q7.2 (S), Q7.3 (S), Q8.1 (S), Q8.2 (S), Q8.3 (S)
unnamed: R28.2, RJ1.14
unnamed: R29.2, RJ1.11
unnamed: C4.2, U3.4 (BTST1)
unnamed: C5.1, U3.19 (BTST2)
unnamed: C7.1, U3.29 (PMID)
unnamed: R1.1, U3.20 (PROG)
unnamed: R10.2, U3.24 (SDRV)
unnamed: R2.2, U3.1 (STAT)
unnamed: R7.2, U3.13 (~CE)
unnamed: R6.2, U3.12 (~QON)
unnamed: R8.1, U6.21 (FSET)
unnamed: R9.1, U6.23 (ISET)
unnamed: C10.1, U6.19 (VLDO)
unnamed: R34.2, U7.5 (VBUS_DET)
unnamed: C30.2, U7.8 (VCC33)
unnamed: C31.1, U7.30 (VDD5)
unnamed: C13.2, U9.8 (BOOT)
unnamed: R11.1, U9.2 (EN)
unnamed: R12.1, U9.3 (FSW)
unnamed: R13.1, U9.19 (ILIM)
unnamed: C14.2, U9.10 (SS)
unnamed: C15.2, U9.1 (VCC)
unnamed: R31.2, U13.7 (HOLD#/RESET#/IO3)
unnamed: R25.2, U13.3 (WP#(IO2))
unnamed: R102.2, U18.45 (CHIPEN)
unnamed: R32.2, U18.38 (OVCUR1J)
unnamed: R33.2, U18.35 (OVCUR2J)
unnamed: R36.2, U18.34 (OVCUR3J/SMC)
unnamed: R37.2, U18.31 (OVCUR4J/SMD)
unnamed: R103.1, U18.53 (PGANG)
unnamed: R101.2, U18.46 (RTERM)
unnamed: L1.2, U18.41 (SW)
unnamed: C226.2, U18.57 (X1), X1.1 (OSC1)
unnamed: C227.1, U18.56 (X2), X1.3 (OSC2)
unnamed: C25.2, U20.5 (DCOUPL)
unnamed: C241.2, U20.18 (DGUARD)
unnamed: R39.2, U20.17 (RBIAS)
unnamed: L5.2, U21.1 (UNBALANCEDPORT)
unnamed: C78.2, U23.11 (AGND)
unnamed: C77.2, U23.10 (CDEC_IN)
unnamed: C77.1, U23.9 (CDEC_OUT)
unnamed: C81.2, U23.16 (DC2)
unnamed: C67.2, U23.4 (DVDD)
unnamed: C80.2, U23.15 (FCAP)
unnamed: C70.2, U23.7 (VDD)
unnamed: U24.5 (RFC), U26.3 (RF2)
unnamed: U25.5 (RFC), U27.3 (RF2)
unnamed: U21.3 (BALANCEDPORT), U26.1 (RF1)
unnamed: R5.1, U37.1 (Terminiation)
unnamed: C93.1, U40.3 (CLPF)
unnamed: C101.2, U40.1 (INHI)
unnamed: R47.1, U40.6 (TADJ)
unnamed: C102.1, U41.3 (CLPF)
unnamed: C100.2, U41.1 (INHI)
unnamed: R50.1, U41.6 (TADJ)
unnamed: C103.1, U42.3 (CLPF)
unnamed: C104.2, U42.1 (INHI)
unnamed: R52.1, U42.6 (TADJ)
unnamed: C117.1, U47.19 (ADCVREF)
unnamed: C114.1, R70.1, U47.16 (HPVDD)
unnamed: C120.2, U47.24 (LIN1)
unnamed: R67.2, U47.1 (MCLK)
unnamed: C119.1, U47.23 (RIN1)
unnamed: C118.2, U47.20 (VMID)
unnamed: C130.1, U50.3 (IN+)
unnamed: C129.2, U51.3 (IN+)
unnamed: C143.1, U59.7 (DVDT)
unnamed: R84.2, R85.2, U59.1 (EN/UVLO)
unnamed: R89.1, U59.9 (ILM)
unnamed: R86.2, R87.2, U59.2 (OVLO/OVCSEL)
unnamed: C146.1, U60.7 (DVDT)
unnamed: R90.2, R92.2, U60.1 (EN/UVLO)
unnamed: R95.1, U60.9 (ILM)
unnamed: R91.2, R93.2, U60.2 (OVLO/OVCSEL)
unnamed: C156.1, R99.1, U62.7 (VREF2), U62.8 (EN)
unnamed: R40.1, USB2.A5 (CC1)
unnamed: R41.1, USB2.B5 (CC2)
PCIE0_CLKREQ: CN4.5, CN6.5, CN9.5, CN10.5, J4.102 (2), J9.52 (~CLKREQ)
PCIE0_PERST: CN4.4, CN6.4, CN9.4, CN10.4, J4.109 (9), J9.50 (~PERST)
PCIE0_REFCLKN: CN4.8, CN6.8, CN9.8, CN10.8, J4.112 (12), J9.53 (REFCLKn)
PCIE0_REFCLKP: CN4.7, CN6.7, CN9.7, CN10.7, J4.110 (10), J9.55 (REFCLKp)
PCIE0_RXN: CN4.14, CN6.14, CN9.14, CN10.14, J4.118 (18), J9.47 (PETn0/SATA-A-)
PCIE0_RXP: CN4.13, CN6.13, CN9.13, CN10.13, J4.116 (16), J9.49 (PETp0/SATA-A+)
PCIE0_TXN: CN4.11, CN6.11, CN9.11, CN10.11, J4.124 (24), J9.41 (PERn0/SATA-B+)
PCIE0_TXP: CN4.10, CN6.10, CN9.10, CN10.10, J4.122 (22), J9.43 (PERp0/SATA-B-)
PCIE0_WAKE: CN4.6, CN6.6, CN9.6, CN10.6, J4.111 (11), J9.54 (~PEWAKE)
PCM_CLK: J9.20 (GPIO_5), U45.10 (COM1)
PCM_IN: J9.22 (GPIO_6), U46.10 (COM1)
PCM_OUT: J9.24 (GPIO_7), U46.6 (COM2)
PCM_SYNC: J9.28 (GPIO_8), U45.6 (COM2)
PWRON: J4.99, SW2.1
RADIO_5V: C67.1, C70.1, C98.1
RADIO_EN: CN15.13, CN16.13, CN19.13, CN20.13, U34.3 (EN), U35.3 (EN), U69.10 (P06)
RADIO_I2C0_SCL: R133.2, U29.7 (I2C_SCL/SPI_SCK), U33.17 (IO9), U64.22 (SCL)
RADIO_I2C0_SDA: R132.1, U29.5 (I2C_SDA/SPI_MISO), U33.12 (IO8), U64.23 (SDA)
RADIO_SPI0_CS: U20.7 (CSn), U33.19 (IO11)
RADIO_SPI0_MISO: U20.2 (SO(GDO1)), U33.18 (IO10)
RADIO_SPI0_MOSI: U20.20 (SI), U33.21 (IO13)
RADIO_SPI0_SCK: U20.1 (SCLK), U33.20 (IO12)
REGN: C3.2, C157.1, R2.1, U3.5 (REGN), U3.17 (ILIM_HIZ)
RESET: J4.92, SW1.1
RFID_ANT1: U23.3 (ANT1), U73.1
RFID_ANT2: U23.6 (ANT2), U73.2
RF_N: U20.13 (RF_N), U27.5 (RFC)
RF_P: U20.12 (RF_P), U26.5 (RFC)
RF_V1: CN15.16, CN16.16, CN19.16, CN20.16, U69.20 (P17), U71.4 (V1)
RF_V2: CN15.18, CN16.18, CN19.18, CN20.18, U69.19 (P16), U71.5 (V2)
RP_ACC_AUX0: CN5.36, CN8.36, CN15.1, CN16.1, CN19.1, CN20.1, CN21.36, CN22.36, U56.2 (NO1), U64.11 (P07)
RP_ACC_AUX1: CN5.37, CN8.37, CN15.2, CN16.2, CN19.2, CN20.2, CN21.37, CN22.37, U56.10 (NO2), U64.13 (P10)
RP_ACC_CS0_N: CN5.33, CN8.33, CN15.6, CN16.6, CN19.6, CN20.6, CN21.33, CN22.33, U33.31 (IO38), U58.10 (NO2)
RP_ACC_IRQ0: CN5.34, CN8.34, CN15.3, CN16.3, CN19.3, CN20.3, CN21.34, CN22.34, U33.36 (RXD0), U57.2 (NO1)
RP_ACC_MISO: CN5.32, CN8.32, CN15.5, CN16.5, CN19.5, CN20.5, CN21.32, CN22.32, U33.28 (IO35), U58.2 (NO1)
RP_ACC_MOSI: CN5.31, CN8.31, CN15.8, CN16.8, CN19.8, CN20.8, CN21.31, CN22.31, U10.10 (NO2), U33.38 (IO2)
RP_ACC_RESET_N: CN5.35, CN8.35, CN15.4, CN16.4, CN19.4, CN20.4, CN21.35, CN22.35, R113.1, U57.10 (NO2), U64.10 (P06)
RP_ACC_SCK: CN5.30, CN8.30, CN15.7, CN16.7, CN19.7, CN20.7, CN21.30, CN22.30, U10.2 (NO1), U33.33 (IO40)
R_BOOST: R14.1, R15.1, U9.17 (FB)
R_UNUSED: R115.2, R116.2, R117.2, R118.2, R119.2, R120.2, R122.2, R126.2, R127.2, R128.2, R129.2, R153.2, U64.5 (P01), U64.15 (P12), U64.16 (P13), U64.17 (P14), U64.18 (P15), U64.19 (P16), U64.20 (P17), U69.14 (P11), U69.15 (P12), U69.16 (P13), U69.17 (P14), U69.18 (P15)
SBU1: U15.10 (COM1), USB1.A8 (SBU1)
SBU2: U15.6 (COM2), USB1.B8 (SBU2)
SC_ACC_AUX0: D5.4 (K), J6.13, R82.1
SC_ACC_AUX1: D5.5 (k), J6.14, R83.1
SC_ACC_CS0_N: D6.5 (k), J6.10, R78.1
SC_ACC_IRQ0: D5.1 (K), J6.11, R77.1
SC_ACC_MISO: D6.4 (K), J6.9, R81.1
SC_ACC_MOSI: D6.3 (K), J6.8, R80.1
SC_ACC_RESET_N: D5.3 (K), J6.12, R79.1
SC_ACC_SCK: D6.1 (K), J6.7, R30.1
SC_ID_SCL: CN5.13, CN21.13, CN22.13, J6.6, U55.14 (SCL), U61.14 (SCL)
SC_ID_SDA: CN5.12, CN21.12, CN22.12, J6.5, U55.15 (SDA), U61.15 (SDA)
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
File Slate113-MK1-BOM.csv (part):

Refs,Value,Footprint,Manufacturer,MPN,LCSC Part,DigiKey Part,Datasheet,Qty,DNP,Unit Price (USD),Total Cost (USD),Price Source
C1,0.1µF,Capacitor_SMD:C_0603_1608Metric,Samsung Electro-Mechanics,CL10B104KB8NNNC,C1591,,,1,,,,
C2,1.0µF,Capacitor_SMD:C_0603_1608Metric,Taiyo Yuden,UMK107BJ105KA-T,C92848,,https://www.lcsc.com/product-detail/C92848.html,1,,,,
C3,4.7µF,Capacitor_SMD:C_0603_1608Metric,Murata Electronics,GRM188R61C475KE11D,C77045,,https://www.lcsc.com/product-detail/C77045.html,1,,,,
C4,47nF,Capacitor_SMD:C_0603_1608Metric,Samsung Electro-Mechanics,0603X7R473J500NT,C49326646,,,1,,,,
C5,47nF,Capacitor_SMD:C_0603_1608Metric,Samsung Electro-Mechanics,0603X7R473J500NT,C49326646,,,1,,,,
C6,10µF,Capacitor_SMD:C_0603_1608Metric,Samsung Electro-Mechanics,TCC0603X5R106M160CT,C380317,,,1,,,,
C7,10µF,Capacitor_SMD:C_0603_1608Metric,Samsung Electro-Mechanics,TCC0603X5R106M160CT,C380317,,,1,,,,
C8,1.0µF,Capacitor_SMD:C_0603_1608Metric,Samsung Electro-Mechanics,CL10A105KA8NNNC,C5673,,https://www.lcsc.com/product-detail/C5673.html,1,,,,
C9,1.0µF,Capacitor_SMD:C_0603_1608Metric,Samsung Electro-Mechanics,CL10A105KA8NNNC,C5673,,https://www.lcsc.com/product-detail/C5673.html,1,,,,
C10,10µF,Capacitor_SMD:C_0603_1608Metric,Samsung Electro-Mechanics,TCC0603X5R106M160CT,C380317,,,1,,,,
C11,4.7µF,Capacitor_SMD:C_0603_1608Metric,Murata Electronics,GRM188R61C475KE11D,C77045,,https://www.lcsc.com/product-detail/C77045.html,1,,,,
C12,2.2µF,Capacitor_SMD:C_0603_1608Metric,Chinocera,HGC0603R5225K500NTHJ,C7432769,,https://www.lcsc.com/product-detail/C7432769.html,1,,,,
C13,100nF,Capacitor_SMD:C_0603_1608Metric,Samsung Electro-Mechanics,CC0603KRX7R9BB104,C14663,,,1,,,,
C14,8.2nF,Capacitor_SMD:C_0603_1608Metric,,0603B822K500NT,C1322360,,,1,,,,
C15,1µF,Capacitor_SMD:C_0603_1608Metric,Samsung Electro-Mechanics,CL10A105KA8NNNC,C5673,,https://www.lcsc.com/product-detail/C5673.html,1,,,,
C16,1nF,Capacitor_SMD:C_0603_1608Metric,Samsung Electro-Mechanics,CC0603KRX7R9BB102,C100040,,,1,,,,
C17,68pF,Capacitor_SMD:C_0603_1608Metric,Samsung Electro-Mechanics,0603CG680J500NT,C1680,,,1,,,,
C18,1µF,Capacitor_SMD:C_0603_1608Metric,Taiyo Yuden,UMK107BJ105KA-T,C92848,,https://www.lcsc.com/product-detail/C92848.html,1,,,,
C19,2.2µF,Capacitor_SMD:C_0603_1608Metric,Samsung Electro-Mechanics,CL10A225KO8NNNC,C23630,,,1,,,,
C20,10µF,Capacitor_SMD:C_0603_1608Metric,Samsung Electro-Mechanics,TCC0603X5R106M160CT,C380317,,,1,,,,
C21,100nF,Capacitor_SMD:C_0603_1608Metric,Samsung Electro-Mechanics,CL10B104KB8NNNC,C1591,,,1,,,,
C22,100nF,Capacitor_SMD:C_0603_1608Metric,Samsung Electro-Mechanics,CL10B104KB8NNNC,C1591,,,1,,,,
C23,100nF,Capacitor_SMD:C_0603_1608Metric,Samsung Electro-Mechanics,CL10B104KB8NNNC,C1591,,,1,,,,
C24,100nF,Capacitor_SMD:C_0603_1608Metric,Samsung Electro-Mechanics,CL10B104KB8NNNC,C1591,,,1,,,,
C25,100nF,Capacitor_SMD:C_0603_1608Metric,Taiyo Yuden,UMK107BJ105KA-T,C92848,,https://www.lcsc.com/product-detail/C92848.html,1,,,,
C26,100nF,Capacitor_SMD:C_0603_1608Metric,Samsung Electro-Mechanics,CL10B104KB8NNNC,C1591,,,1,,,,
C27,100nF,Capacitor_SMD:C_0603_1608Metric,Samsung Electro-Mechanics,CL10B104KB8NNNC,C1591,,,1,,,,
C28,15pF,Capacitor_SMD:C_0402_1005Metric,,0402CG270J500NT,C1557,,,1,,,,
C29,15pF,Capacitor_SMD:C_0402_1005Metric,,0402CG270J500NT,C1557,,,1,,,,
C30,100nF,Capacitor_SMD:C_0603_1608Metric,Samsung Electro-Mechanics,CL10B104KB8NNNC,C1591,,,1,,,,
C31,100nF,Capacitor_SMD:C_0603_1608Metric,Samsung Electro-Mechanics,CL10B104KB8NNNC,C1591,,,1,,,,
C32,2.2µF,Capacitor_SMD:C_0603_1608Metric,Samsung Electro-Mechanics,CL10A225KO8NNNC,C23630,,,1,,,,
C33,100nF,Capacitor_SMD:C_0603_1608Metric,Samsung Electro-Mechanics,CL10B104KB8NNNC,C1591,,,1,,,,
C34,100nF,Capacitor_SMD:C_0603_1608Metric,Samsung,CL10B104KB8NNNC,C1591,,,1,,,,
C35,20pF,Capacitor_SMD:C_0402_1005Metric,,0402CG200J500NT,C1554,,,1,,,,
C36,100nF,Capacitor_SMD:C_0603_1608Metric,Samsung Electro-Mechanics,CL10B104KB8NNNC,C1591,,,1,,,,
C37,100nF,Capacitor_SMD:C_0603_1608Metric,Samsung Electro-Mechanics,CL10B104KB8NNNC,C1591,,,1,,,,
C38,100nF,Capacitor_SMD:C_0603_1608Metric,Samsung Electro-Mechanics,CL10B104KB8NNNC,C1591,,,1,,,,
C39,100nF,Capacitor_SMD:C_0603_1608Metric,Samsung Electro-Mechanics,CL10B104KB8NNNC,C1591,,,1,,,,
C40,100nF,Capacitor_SMD:C_0603_1608Metric,Samsung Electro-Mechanics,CL10B104KB8NNNC,C1591,,,1,,,,
C41,100nF,Capacitor_SMD:C_0603_1608Metric,Samsung Electro-Mechanics,CL10B104KB8NNNC,C1591,,,1,,,,
C42,2.2µF,Capacitor_SMD:C_0603_1608Metric,Samsung Electro-Mechanics,CL10A225KO8NNNC,C23630,,,1,,,,
C43,100nF,Capacitor_SMD:C_0603_1608Metric,Samsung Electro-Mechanics,CL10B104KB8NNNC,C1591,,,1,,,,
C44,100nF,Capacitor_SMD:C_0603_1608Metric,Samsung Electro-Mechanics,CL10B104KB8NNNC,C1591,,,1,,,,
C45,100nF,Capacitor_SMD:C_0603_1608Metric,Samsung Electro-Mechanics,CL10B104KB8NNNC,C1591,,,1,,,,
C46,100nF,Capacitor_SMD:C_0603_1608Metric,Samsung Electro-Mechanics,CL10B104KB8NNNC,C1591,,,1,,,,
C47,100nF,Capacitor_SMD:C_0603_1608Metric,Samsung Electro-Mechanics,CL10B104KB8NNNC,C1591,,,1,,,,
C48,100nF,Capacitor_SMD:C_0603_1608Metric,Samsung Electro-Mechanics,CL10B104KB8NNNC,C1591,,,1,,,,
C49,100nF,Capacitor_SMD:C_0603_1608Metric,Samsung Electro-Mechanics,CL10B104KB8NNNC,C1591,,,1,,,,
C50,100nF,Capacitor_SMD:C_0603_1608Metric,Samsung Electro-Mechanics,CL10B104KB8NNNC,C1591,,,1,,,,
C51,100nF,Capacitor_SMD:C_0603_1608Metric,Samsung Electro-Mechanics,CL10B104KB8NNNC,C1591,,,1,,,,
C52,100nF,Capacitor_SMD:C_0603_1608Metric,Samsung Electro-Mechanics,CL10B104KB8NNNC,C1591,,,1,,,,
C53,100nF,Capacitor_SMD:C_0603_1608Metric,Samsung Electro-Mechanics,CL10B104KB8NNNC,C1591,,,1,,,,
C54,100nF,Capacitor_SMD:C_0603_1608Metric,Samsung Electro-Mechanics,CL10B104KB8NNNC,C1591,,,1,,,,
C55,100nF,Capacitor_SMD:C_0603_1608Metric,Samsung Electro-Mechanics,CL10B104KB8NNNC,C1591,,,1,,,,
C56,100nF,Capacitor_SMD:C_0603_1608Metric,Samsung Electro-Mechanics,CL10B104KB8NNNC,C1591,,,1,,,,
C57,100nF,Capacitor_SMD:C_0603_1608Metric,Samsung Electro-Mechanics,TCC0603X5R106M160CT,C380317,,,1,,,,
C58,100nF,Capacitor_SMD:C_0603_1608Metric,Samsung Electro-Mechanics,TCC0603X5R106M160CT,C380317,,,1,,,,
C59,100nF,Capacitor_SMD:C_0603_1608Metric,Samsung Electro-Mechanics,TCC0603X5R106M160CT,C380317,,,1,,,,
C60,1.8pF,Capacitor_SMD:C_0402_1005Metric,,C1005NPO189CGT,C258489,,,1,,,,
C61,10µF,Capacitor_SMD:C_0603_1608Metric,CCTC,TCC0603X5R106M160CT,C380317,,,1,,,,
C62,100nF,Capacitor_SMD:C_0603_1608Metric,Samsung,CL10B104KB8NNNC,C1591,,,1,,,,
C63,100pF,Capacitor_SMD:C_0603_1608Metric,Samsung Electro-Mechanics,CL10C101JB8NNNC,C14858,,,1,,,,
C64,6.8pF,Capacitor_SMD:C_0402_1005Metric,Samsung Electro-Mechanics,0402CG6R8C500NT,C1576,,,1,,,,
C65,6.8 pF ± 0.5 pF,Capacitor_SMD:C_0402_1005Metric,Samsung Electro-Mechanics,0402CG6R8C500NT,C1576,,,1,,,,
C66,20pF,Capacitor_SMD:C_0402_1005Metric,,0402CG200J500NT,C1554,,,1,,,,
C67,100nF,Capacitor_SMD:C_0603_1608Metric,,CL10B104KB8NNNC,C1591,,,1,,,,
C68,4.7µF,Capacitor_SMD:C_0603_1608Metric,,CL10A475KO8NNNC,C19666,,,1,,,,
C69,100nF,Capacitor_SMD:C_0603_1608Metric,Samsung Electro-Mechanics,CL10B104KB8NNNC,C1591,,,1,,,,
C70,100nF,Capacitor_SMD:C_0603_1608Metric,Samsung Electro-Mechanics,CL10B104KB8NNNC,C1591,,,1,,,,
C71,4.7µF,Capacitor_SMD:C_0603_1608Metric,,CL10A475KO8NNNC,C19666,,,1,,,,
C72,2.2µF,Capacitor_SMD:C_0603_1608Metric,,CL10A225KO8NNNC,C23630,,,1,,,,
C73,100nF,Capacitor_SMD:C_0603_1608Metric,,CL10B104KB8NNNC,C1591,,,1,,,,
C74,2.2µF,Capacitor_SMD:C_0603_1608Metric,,CL10A225KO8NNNC,C23630,,,1,,,,
C75,2.2µF,Capacitor_SMD:C_0603_1608Metric,Samsung Electro-Mechanics,CL10A225KO8NNNC,C23630,,,1,,,,
C76,1µF,Capacitor_SMD:C_0603_1608Metric,Taiyo Yuden,UMK107BJ105KA-T,C92848,,https://www.lcsc.com/product-detail/C92848.html,1,,,,
C77,100nF,Capacitor_SMD:C_0603_1608Metric,,CL10B104KB8NNNC,C1591,,,1,,,,
C78,100nF,Capacitor_SMD:C_0603_1608Metric,,CL10B104KB8NNNC,C1591,,,1,,,,
C79,2.2µF,Capacitor_SMD:C_0603_1608Metric,Samsung Electro-Mechanics,CL10A225KO8NNNC,C23630,,,1,,,,
C80,10nF,Capacitor_SMD:C_0603_1608Metric,,0603X7R103J500NT,C49326600,,,1,,,,
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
